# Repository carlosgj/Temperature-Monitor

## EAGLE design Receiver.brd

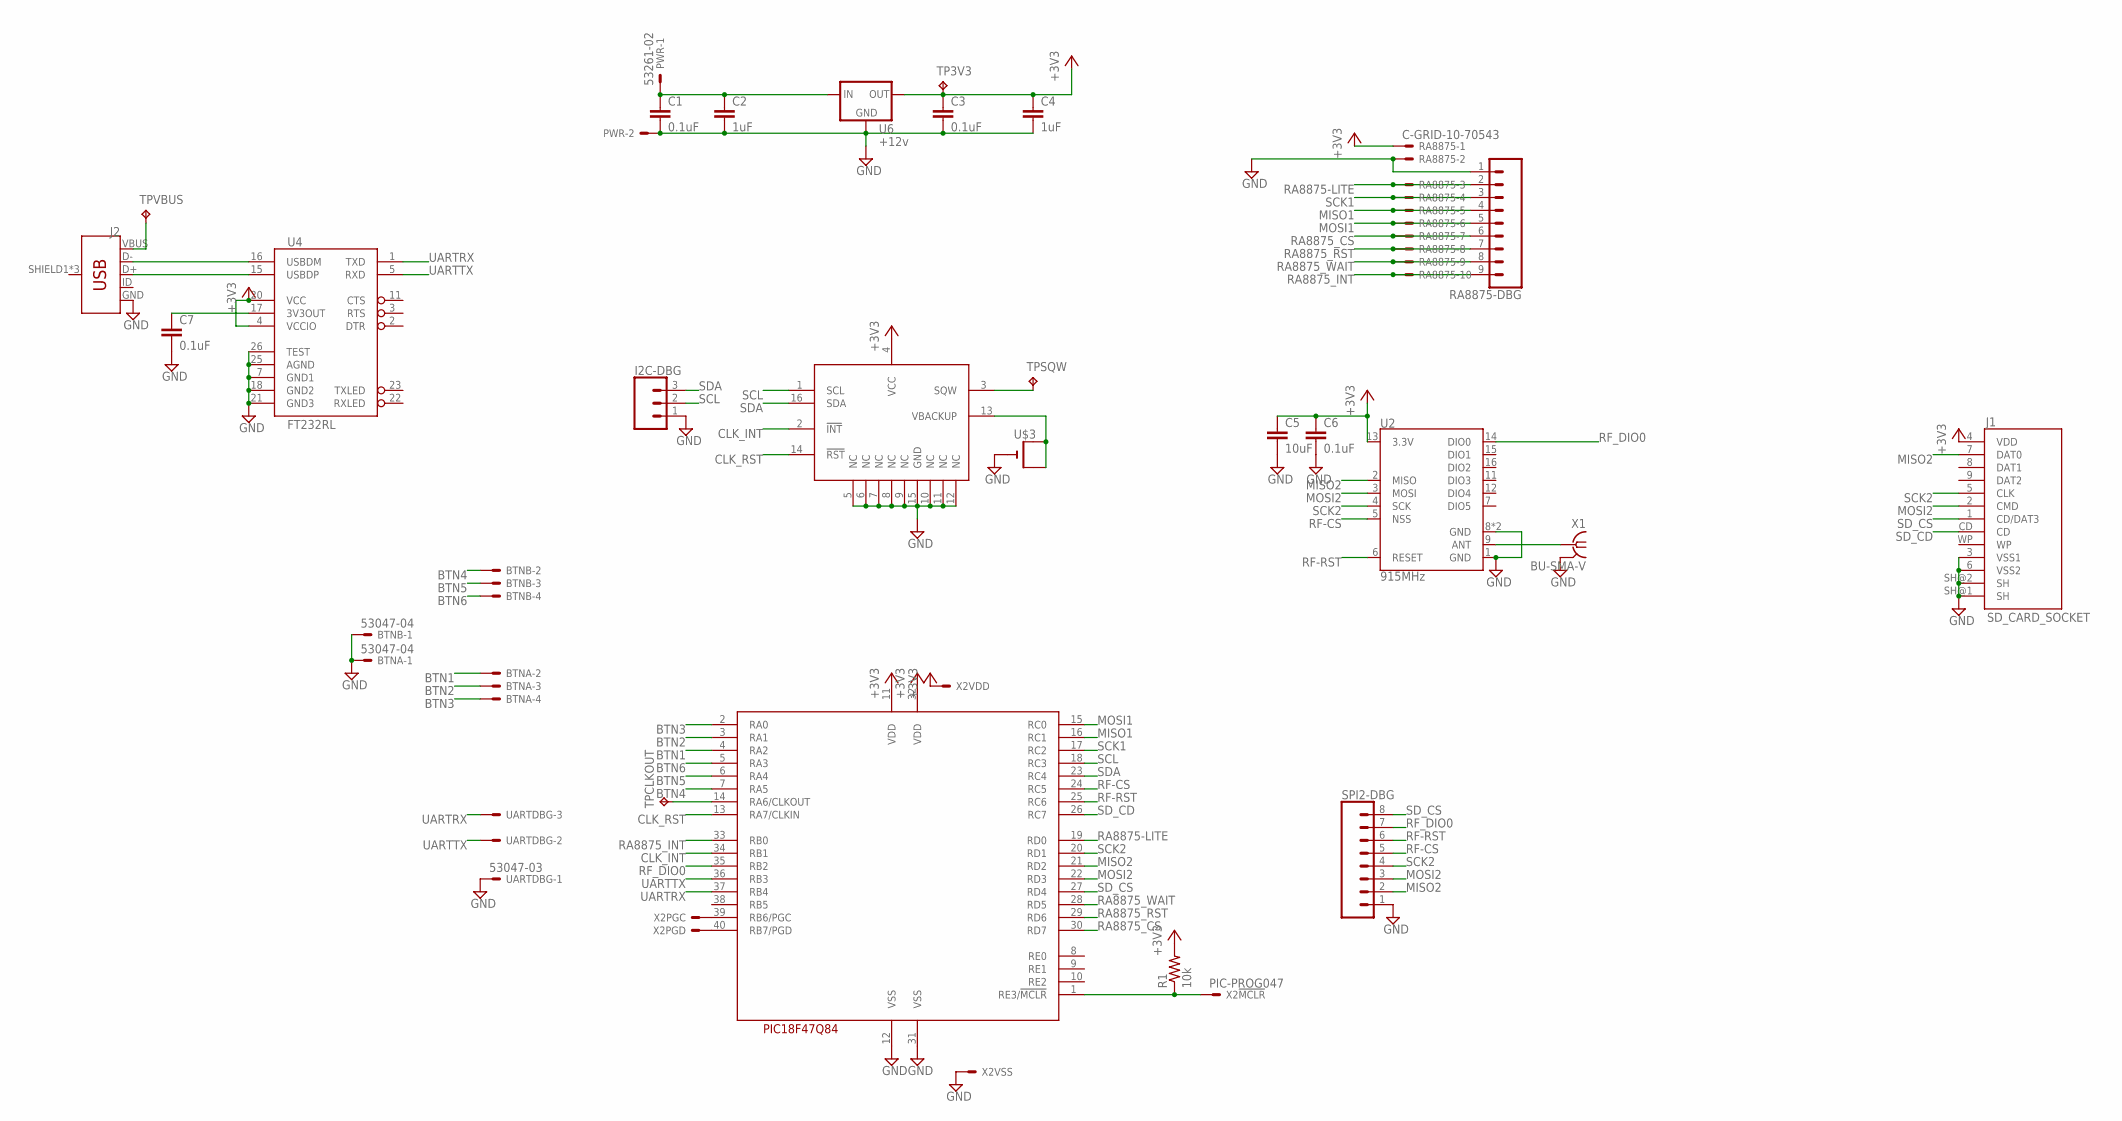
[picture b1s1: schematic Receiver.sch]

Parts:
BTNA: 53047-04
BTNB: 53047-04
C1, C3, C6, C7: 0.1uF; C1206
C2, C4: 1uF; C1206
C5: 10uF; C1206
I2C-DBG: CONN_03; 1X03
J1: SD_CARD_SOCKET; SD
J2: USB_MICRO-B_FEMALE-SMT; USB-B-MICRO-SMD
PWR: 53261-02
R1: 10k; R1206
RA8875: C-GRID-10-70543; 70543-10
RA8875-DBG: CONN_09; 1X09
SPI2-DBG: CONN_08"; 1X08
TP3V3: TPB2,54; B2,54
TPCLKOUT: TPB2,54; B2,54
TPSQW: TPB2,54; B2,54
TPVBUS: TPB2,54; B2,54
U1: PIC18F47Q84; DIL40
U2: 915MHz; RFM69HCW-XXXS2
U4: FT232RL; SSOP28DB
U5: DS1374C; SO-16DW
U6: +12v; TO-252
U$3: CR1220SMT; CR1220-SMD
UARTDBG: 53047-03
X1: BU-SMA-V
X2: PIC-PROG047; 53047-05

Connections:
+3V3: C3.1, C4.1, C5.1, C6.1, J1.4 (VDD), R1.2, RA8875.1, TP3V3.TP, U1.11 (VDD), U1.32 (VDD), U2.13 (3.3V), U4.4 (VCCIO), U4.20 (VCC), U5.4 (VCC), U6.2 (OUT), X2.2
BTN1: BTNA.2, U1.4 (RA2)
BTN2: BTNA.3, U1.3 (RA1)
BTN3: BTNA.4, U1.2 (RA0)
BTN4: BTNB.2, U1.7 (RA5)
BTN5: BTNB.3, U1.6 (RA4)
BTN6: BTNB.4, U1.5 (RA3)
CLK_INT: U1.34 (RB1), U5.2 (!INT)
CLK_RST: U1.13 (RA7/CLKIN), U5.14 (!RST)
GND: BTNA.1, BTNB.1, C1.2, C2.2, C3.2, C4.2, C5.2, C6.2, C7.2, I2C-DBG.1, J1.3 (VSS1), J1.6 (VSS2), J1.SH@1 (SH), J1.SH@2 (SH), J2.GND, PWR.2, RA8875.2, RA8875-DBG.1, SPI2-DBG.1, U1.12 (VSS), U1.31 (VSS), U2.1 (GND), U2.8 (GND), U2.10 (GND), U4.7 (GND1), U4.18 (GND2), U4.21 (GND3), U4.25 (AGND), U4.26 (TEST), U5.5 (NC), U5.6 (NC), U5.7 (NC), U5.8 (NC), U5.9 (NC), U5.10 (NC), U5.11 (NC), U5.12 (NC), U5.15 (GND), U6.3 (GND), U$3.-, UARTDBG.1, X1.2, X1.3 (2), X1.4 (2), X1.5 (2), X2.3
MISO1: RA8875.5, RA8875-DBG.4, U1.16 (RC1)
MISO2: J1.7 (DAT0), SPI2-DBG.2, U1.21 (RD2), U2.2 (MISO)
MOSI1: RA8875.6, RA8875-DBG.5, U1.15 (RC0)
MOSI2: J1.2 (CMD), SPI2-DBG.3, U1.22 (RD3), U2.3 (MOSI)
unnamed: U1.39 (RB6/PGC), X2.5
unnamed: U1.40 (RB7/PGD), X2.4
unnamed: R1.1, U1.1 (RE3/!MCLR), X2.1
unnamed: C1.1, C2.1, PWR.1, U6.1 (IN)
unnamed: J2.VBUS, TPVBUS.TP
unnamed: C7.1, U4.17 (3V3OUT)
unnamed: J2.D-, U4.16 (USBDM)
unnamed: J2.D+, U4.15 (USBDP)
unnamed: U5.13 (VBACKUP), U$3.+$1 (+), U$3.+$2 (+1)
unnamed: TPSQW.TP, U5.3 (SQW)
unnamed: TPCLKOUT.TP, U1.14 (RA6/CLKOUT)
unnamed: U2.9 (ANT), X1.1
RA8875-LITE: RA8875.3, RA8875-DBG.2, U1.19 (RD0)
RA8875_CS: RA8875.7, RA8875-DBG.6, U1.30 (RD7)
RA8875_INT: RA8875.10, RA8875-DBG.9, U1.33 (RB0)
RA8875_RST: RA8875.8, RA8875-DBG.7, U1.29 (RD6)
RA8875_WAIT: RA8875.9, RA8875-DBG.8, U1.28 (RD5)
RF-CS: SPI2-DBG.5, U1.24 (RC5), U2.5 (NSS)
RF-RST: SPI2-DBG.6, U1.25 (RC6), U2.6 (RESET)
RF_DIO0: SPI2-DBG.7, U1.35 (RB2), U2.14 (DIO0)
SCK1: RA8875.4, RA8875-DBG.3, U1.17 (RC2)
SCK2: J1.5 (CLK), SPI2-DBG.4, U1.20 (RD1), U2.4 (SCK)
SCL: I2C-DBG.2, U1.18 (RC3), U5.1 (SCL)
SDA: I2C-DBG.3, U1.23 (RC4), U5.16 (SDA)
SD_CD: J1.CD, U1.26 (RC7)
SD_CS: J1.1 (CD/DAT3), SPI2-DBG.8, U1.27 (RD4)
UARTRX: U1.37 (RB4), U4.1 (TXD), UARTDBG.3
UARTTX: U1.36 (RB3), U4.5 (RXD), UARTDBG.2

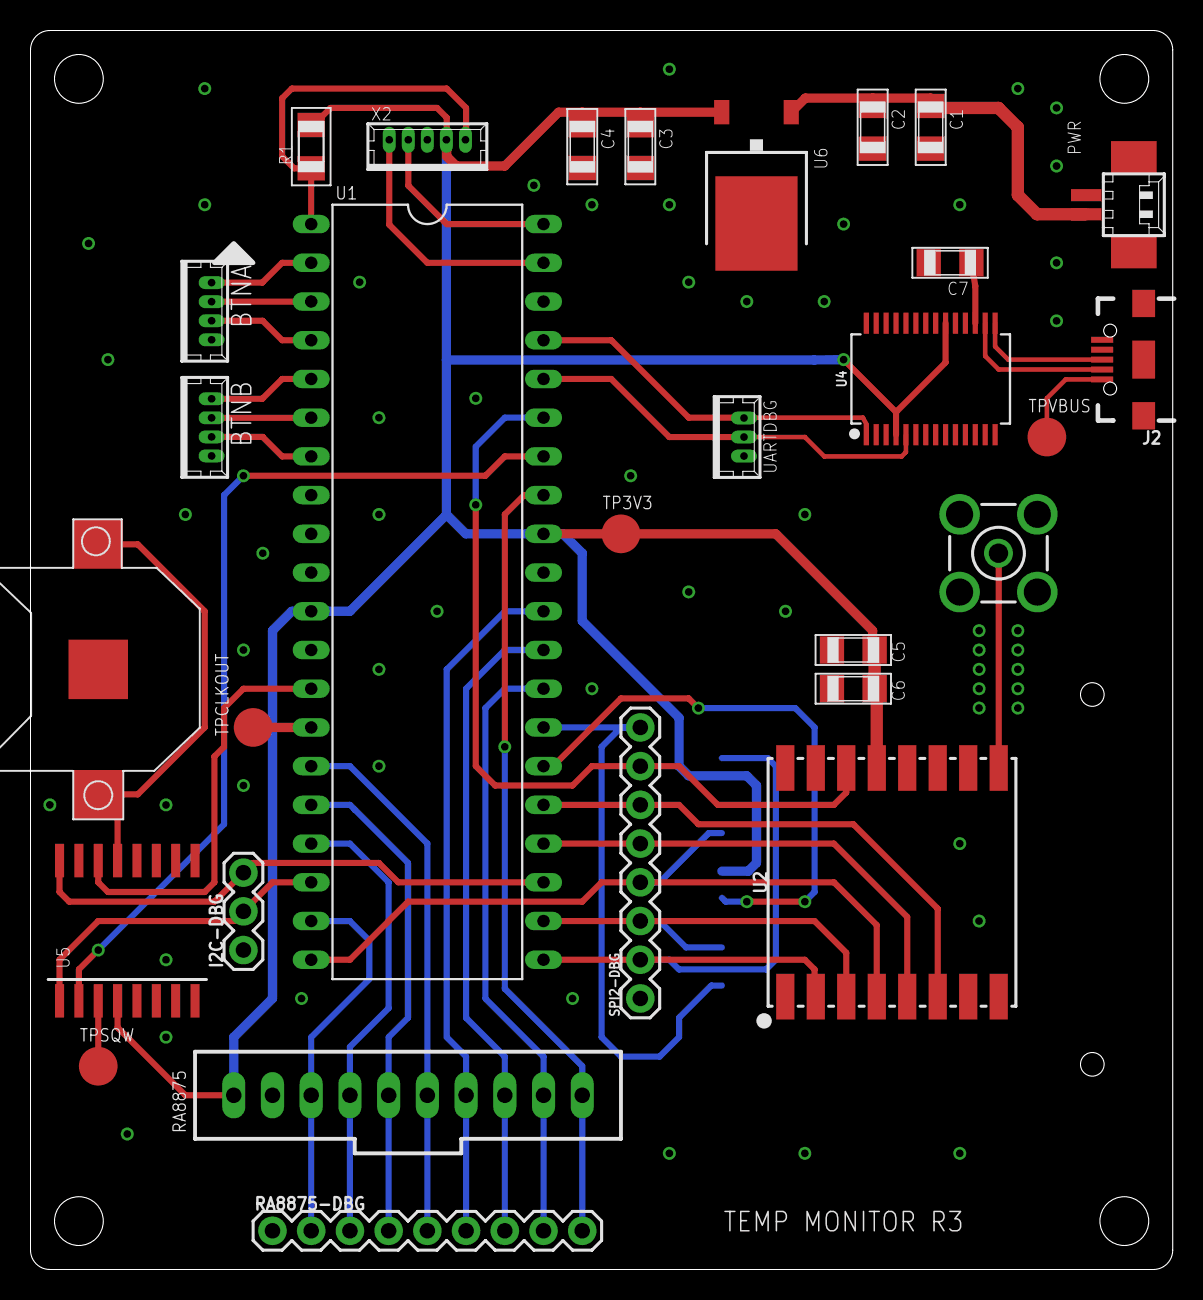
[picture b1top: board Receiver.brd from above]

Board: 2 copper layers, 74.9 x 81.3 mm, 30 parts (1 on the bottom side), 42 nets.

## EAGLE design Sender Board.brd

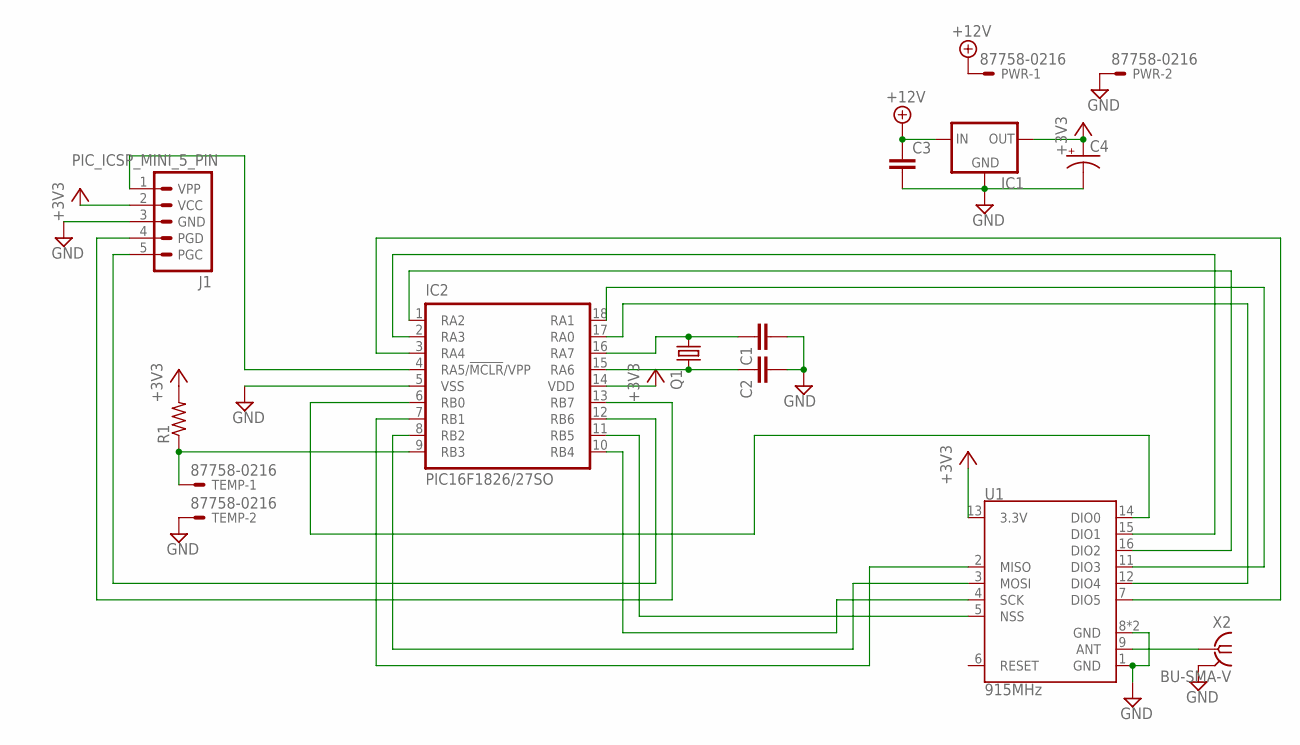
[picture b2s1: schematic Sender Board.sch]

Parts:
C1, C2: C-EUC1206; C1206
C3: C-EU050-025X075; C050-025X075
C4: CPOL-USE3.5-8; E3,5-8
IC1: 78LXX
IC2: PIC16F1826/27SO; SO-18W
J1: PIC_ICSP_MINI_5_PIN
PWR: 87758-0216
Q1: CRYSTALTC26V; TC26V
R1: R-US_0204/7; 0204/7
TEMP: 87758-0216
U1: 915MHz; RFM69HCW-XXXS2
X2: BU-SMA-V

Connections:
+3V3: C4.+, IC1.OUT, IC2.14 (VDD), J1.2 (VCC), R1.2, U1.13 (3.3V)
+12V: C3.1, IC1.IN, PWR.1
GND: C1.2, C2.2, C3.2, C4.-, IC1.GND, IC2.5 (VSS), J1.3 (GND), PWR.2, TEMP.2, U1.1 (GND), U1.8 (GND), U1.10 (GND), X2.2, X2.3 (2), X2.4 (2), X2.5 (2)
MISO: IC2.7 (RB1), U1.2 (MISO)
MOSI: IC2.8 (RB2), U1.3 (MOSI)
unnamed: IC2.13 (RB7), J1.4 (PGD)
unnamed: IC2.12 (RB6), J1.5 (PGC)
unnamed: IC2.4 (RA5/!MCLR!/VPP), J1.1 (VPP)
unnamed: C1.1, IC2.16 (RA7), Q1.1
unnamed: C2.1, IC2.15 (RA6), Q1.2
unnamed: IC2.6 (RB0), U1.14 (DIO0)
unnamed: U1.9 (ANT), X2.1
unnamed: IC2.9 (RB3), R1.1, TEMP.1
unnamed: IC2.11 (RB5), U1.5 (NSS)
unnamed: IC2.18 (RA1), U1.11 (DIO3)
unnamed: IC2.17 (RA0), U1.12 (DIO4)
unnamed: IC2.1 (RA2), U1.16 (DIO2)
unnamed: IC2.2 (RA3), U1.15 (DIO1)
unnamed: IC2.3 (RA4), U1.7 (DIO5)
SCK: IC2.10 (RB4), U1.4 (SCK)

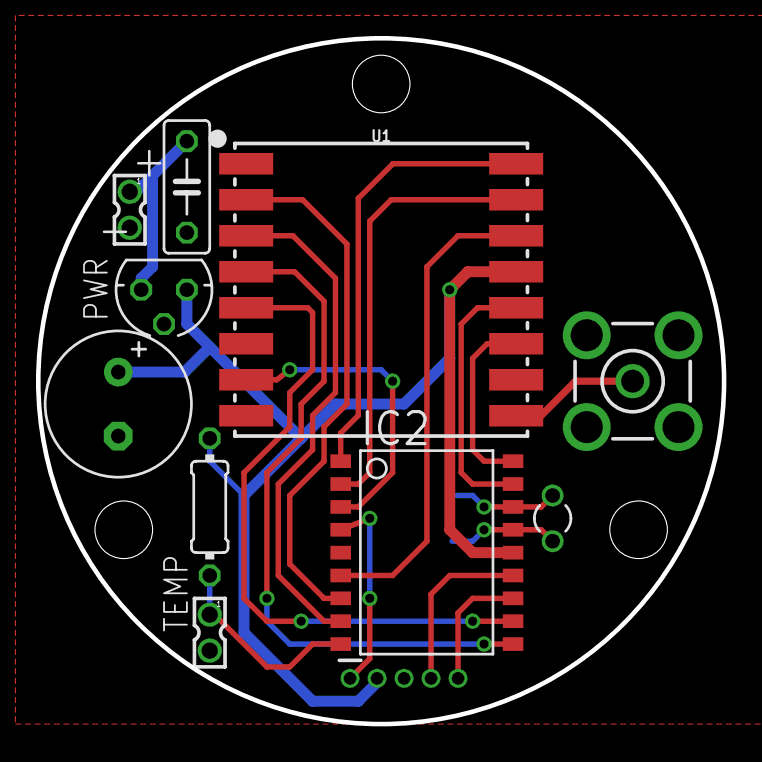
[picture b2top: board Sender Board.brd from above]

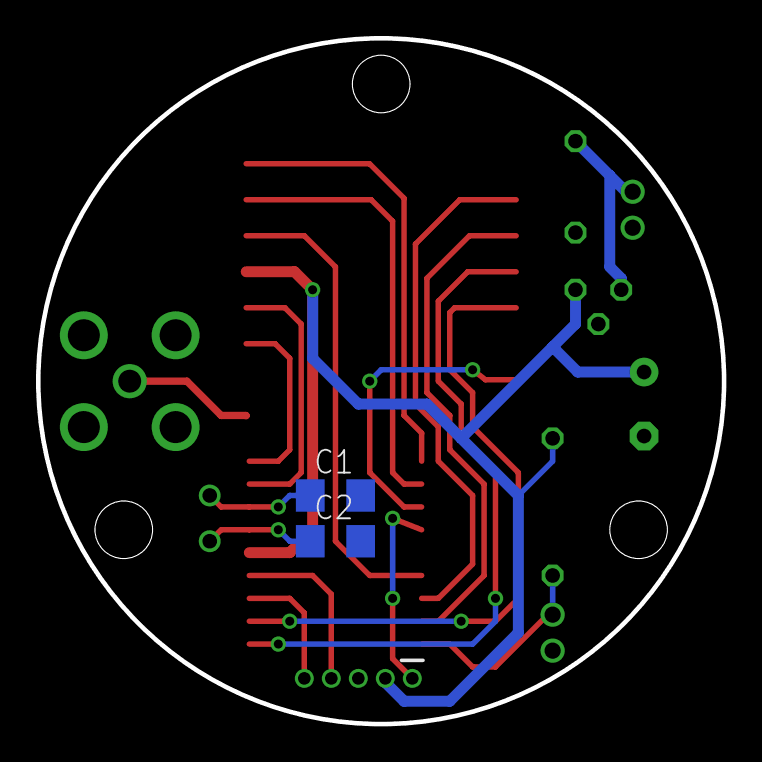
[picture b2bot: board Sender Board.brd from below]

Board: 2 copper layers, 38.1 x 38.1 mm, 13 parts (2 on the bottom side), 20 nets.

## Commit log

2017-09-07 Initial
2017-09-08 no message
2017-09-22 Ordered sender PCB
2017-10-20 Initial code
2017-11-10 Started work on code for RFM69HCW
2018-11-20 Updated receiver PCB
2018-11-23 Working on display testing
2018-11-23 Sender mech updates
2018-12-01 RTC works
2018-12-01 RTC integrated
2018-12-01 ms timer works
2018-12-02 Integrated radio (not working) Integrated display (working)
2018-12-02 Aluminum front panel
2018-12-05 Integration work
2018-12-18 Old stuff
2018-12-18 GUI working well
2018-12-19 Working memory management
2018-12-19 New RTC seems to oscillate
2018-12-22 RTC works!
2018-12-23 Thermometer works
2018-12-23 Working out bugs in page setup
2018-12-24 Actual data display working
2018-12-24 Implementing graph modes
2018-12-25 Time setting and safe mode
2018-12-25 Removing old stuff
2019-11-08 Sender stuff
2019-11-08 CAM work
2019-11-09 More CAM on sender
2019-12-28 Adding bottom
2021-12-21 COSMOS
2021-12-21 Arduino stuff
2021-12-21 Random crap
2021-12-21 Long-overdue bugfixes
2021-12-21 Gitignore
2021-12-23 Kinda okay?
2023-12-29 Old stuff, apparently
2023-12-30 Receiver board r2
2024-01-30 Working on code for new processor
2024-01-30 Adding button inputs
2024-01-30 Reorganizing RTC code
2024-01-30 Importing FAT fs code
2024-01-31 Syntactic changes to remove warnings
2024-01-31 Splitting out UI stuff
2024-01-31 PCB updates
    - Connected NC pins of DS1374 to GND
    - Connected CLK_RST to PIC
    - Moved I2C to default pins on PIC
2024-01-31 Working on adapting Python datetime routines
2024-01-31 Board mount
2024-01-31 Updating to correct processor
2024-01-31 Working on datetime routines
2024-02-01 Debugging SD card
2024-02-01 SD card write works!
2024-02-02 Cleaning up unneeded files
2024-02-02 Cleaning up types to remove warnings
2024-02-02 Cleaning up SD card code
2024-02-02 Trying to re-add some 18CXX stuff
2024-02-02 Incorporating (old) RFM69 code
2024-02-02 Updating RTC types
2024-02-02 Implementing fast SD SPI
2024-02-02 Restructuring cyclic exec
2024-02-03 Renaming time to timers to avoid conflict with C time lib
2024-02-03 Working on implementing application logic
2024-02-03 Getting some basic datetime routines working
2024-02-05 Getting RFM69 SPI working
2024-02-05 Tidying up init messages
2024-02-08 PIC receive works! Lot of cleanup to do...
2024-02-09 RF link is working and parsing data correctly
2024-02-11 Starting to refactor for R2.1 PCB
2024-02-11 More board refactoring (RF works)
2024-02-11 Adding hardware SD card detect
2024-02-11 Making RTC init prettier
2024-02-15 Improving debug messages

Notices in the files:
parts and their libraries:
SparkFun-RF: Licensing: Creative Commons ShareAlike 4.0 International - https://creativecommons.org/licenses/by-sa/4.0
